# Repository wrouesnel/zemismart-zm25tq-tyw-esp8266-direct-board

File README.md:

# ESP8266 Adapter Board for Zemismart ZM25TQ-TYW Tubular Motor

This is a PCB I designed for doing an ESP chip swap on the Zemismart ZM25TQ-TYW tubular motor.

It allows a simple direct replacement of the WBR1 microcontroller board, which rides on a carrier shim to
mate with the motorized blind itself. Communication happens over serial using the Tuya protocol, so ESPHome
can speak to it easily.

The carrier board in the motor tube is marked `TYWBR1_VER 0.0 210131`. The PCB in this repository is
designed to be a direct replacement for it, carrying an ESP-07 or ESP-07S (ESP-07S recommended).

You want to use the ESP-07 series because of the on-board SMA connector, which allows using the included antenna
with the tubular motor directly. You need to remove a 0 ohm resistor from these boards to use the external antenna.

The resistor to remove is shown below - the pads closest to the chip.

## Production

The [JLCPCB production files](jlcbpcb/production_files) I used for this board are included, use the SMD single-sided assembly service - all parts
are basic resistors which costs cents for assembly.

One consideration with production was I used the default PCB thickness - this worked fine, but a thinner PCB might
be better since castellate solder pads cost considerably more - and a little less height will help with the workaround
for soldering.

## Usage

**NOTE**: these instructions assume you know what you are doing. If this all seems to daunting, please don't plough
ahead anyway.

Make sure you flash your ESP with ESPHome before assembling everything! How to do this is described well elsewhere.
The ESPHome configuration to set the motor up as a [generic blind](esphome/generic-zemismart-zm25tq-tyw.yaml) is here.
I recommend customizing it for your use case (namely: set it up to auto-connect to your wifi, I've also added a required
secret for the fallback-wifi-password - you don't want that to default to open).

The motor comes apart fairly easily - just undo the screws (the design seems to have improved since the first one
I bought which required more force). I did have to desolder the reset switch to get it out. Take pictures while
you disassemble so you can re-assemble.

The image below shows the two boards side by side sitting on top of the blind motor board.

The easiest way to desolder this board is to add more solder to bridge all the pads, then use the soldering iron to
heat the blob up to liquid. There's tape underneath the chip, so use a small screw-driver to get the board up. Make
sure the solder is melted though - the traces underneath are fragile and can get lifted doing this (though there are
ways to repair it).

Showing the chip and the tape...

Use a desoldering gun or some solder wick to clean up the pads. I have a cheap desoldering station which works great.

I put red electrical tape over the white section of the mask to cover the test pads - these have 24V when the motor
is powered, so it's just some extra insulation.

The PCB doesn't have castellate pads - they add a considerable premium. The two possible solutions are to file the pads
on the edge till the open up, or to do a kind of careful solder bridge over the edge. I opted for the latter, but it
is is tricky - try what works best (I'll try the pseudo-castellation next time round).

The original PCB is hot glued down to provide support. I used electrical tape to cover the pseudo-castellations and the
top of the IPEX antenna. The final product looks like this, and fits back in the tube nicely.

And taped up:

When it's all back together, it's seamless - but maybe put a label on it so you know it's been chip-swapped (also
which specifies the name of the chip you put in - there's a lot of options you could go with).

### Will it work elsewhere?

Probably! I suspect this carrier board is pretty common. The Zemismart motor design has been improved and disassembled
quite well, so having the carrier board in hand made swapping it out a breeze.

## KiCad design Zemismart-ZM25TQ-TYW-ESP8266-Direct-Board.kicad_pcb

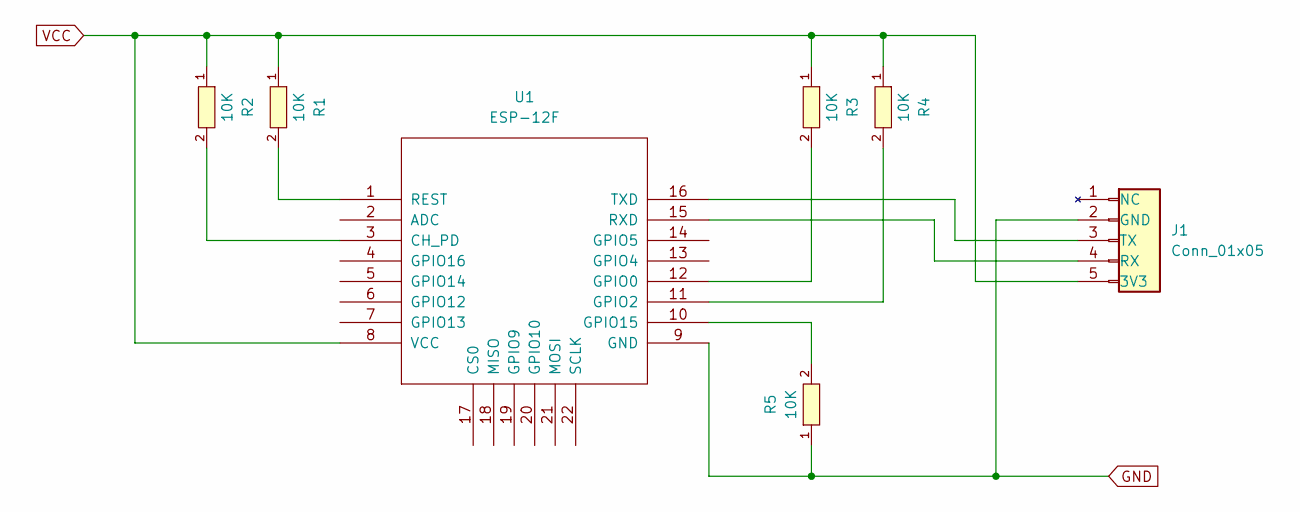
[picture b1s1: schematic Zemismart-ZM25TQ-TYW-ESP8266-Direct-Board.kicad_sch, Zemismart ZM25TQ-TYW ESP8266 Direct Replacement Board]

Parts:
J1: Conn_01x05; JST_PH_B5B-PH-K_1x05_P2.00mm_Vertical
R1, R2, R3, R4, R5: 10K; R0402; LCSC C25744
U1: ESP-12F; ESP-12E_SMD

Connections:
GND: J1.2 (GND), R5.1, U1.9 (GND)
unnamed: J1.4 (RX), U1.15 (RXD)
unnamed: J1.3 (TX), U1.16 (TXD)
unnamed: R2.2, U1.3 (CH_PD)
unnamed: R3.2, U1.12 (GPIO0)
unnamed: R4.2, U1.11 (GPIO2)
unnamed: R5.2, U1.10 (GPIO15)
unnamed: R1.2, U1.1 (REST)
VCC: J1.5 (3V3), R1.1, R2.1, R3.1, R4.1, U1.8 (VCC)

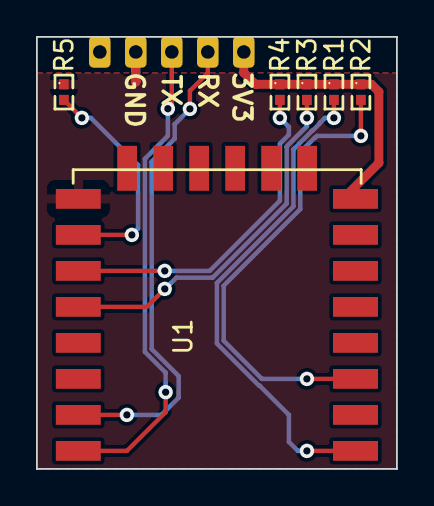
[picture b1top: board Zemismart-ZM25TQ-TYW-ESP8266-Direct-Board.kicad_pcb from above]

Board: 2 copper layers, 20.0 x 24.0 mm, 7 parts (0 on the bottom side), 9 nets.

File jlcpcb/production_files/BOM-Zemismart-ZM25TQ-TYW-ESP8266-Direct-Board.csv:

Comment,Designator,Footprint,LCSC
10K,"R1,R2,R3,R4,R5",R0402,C25744
